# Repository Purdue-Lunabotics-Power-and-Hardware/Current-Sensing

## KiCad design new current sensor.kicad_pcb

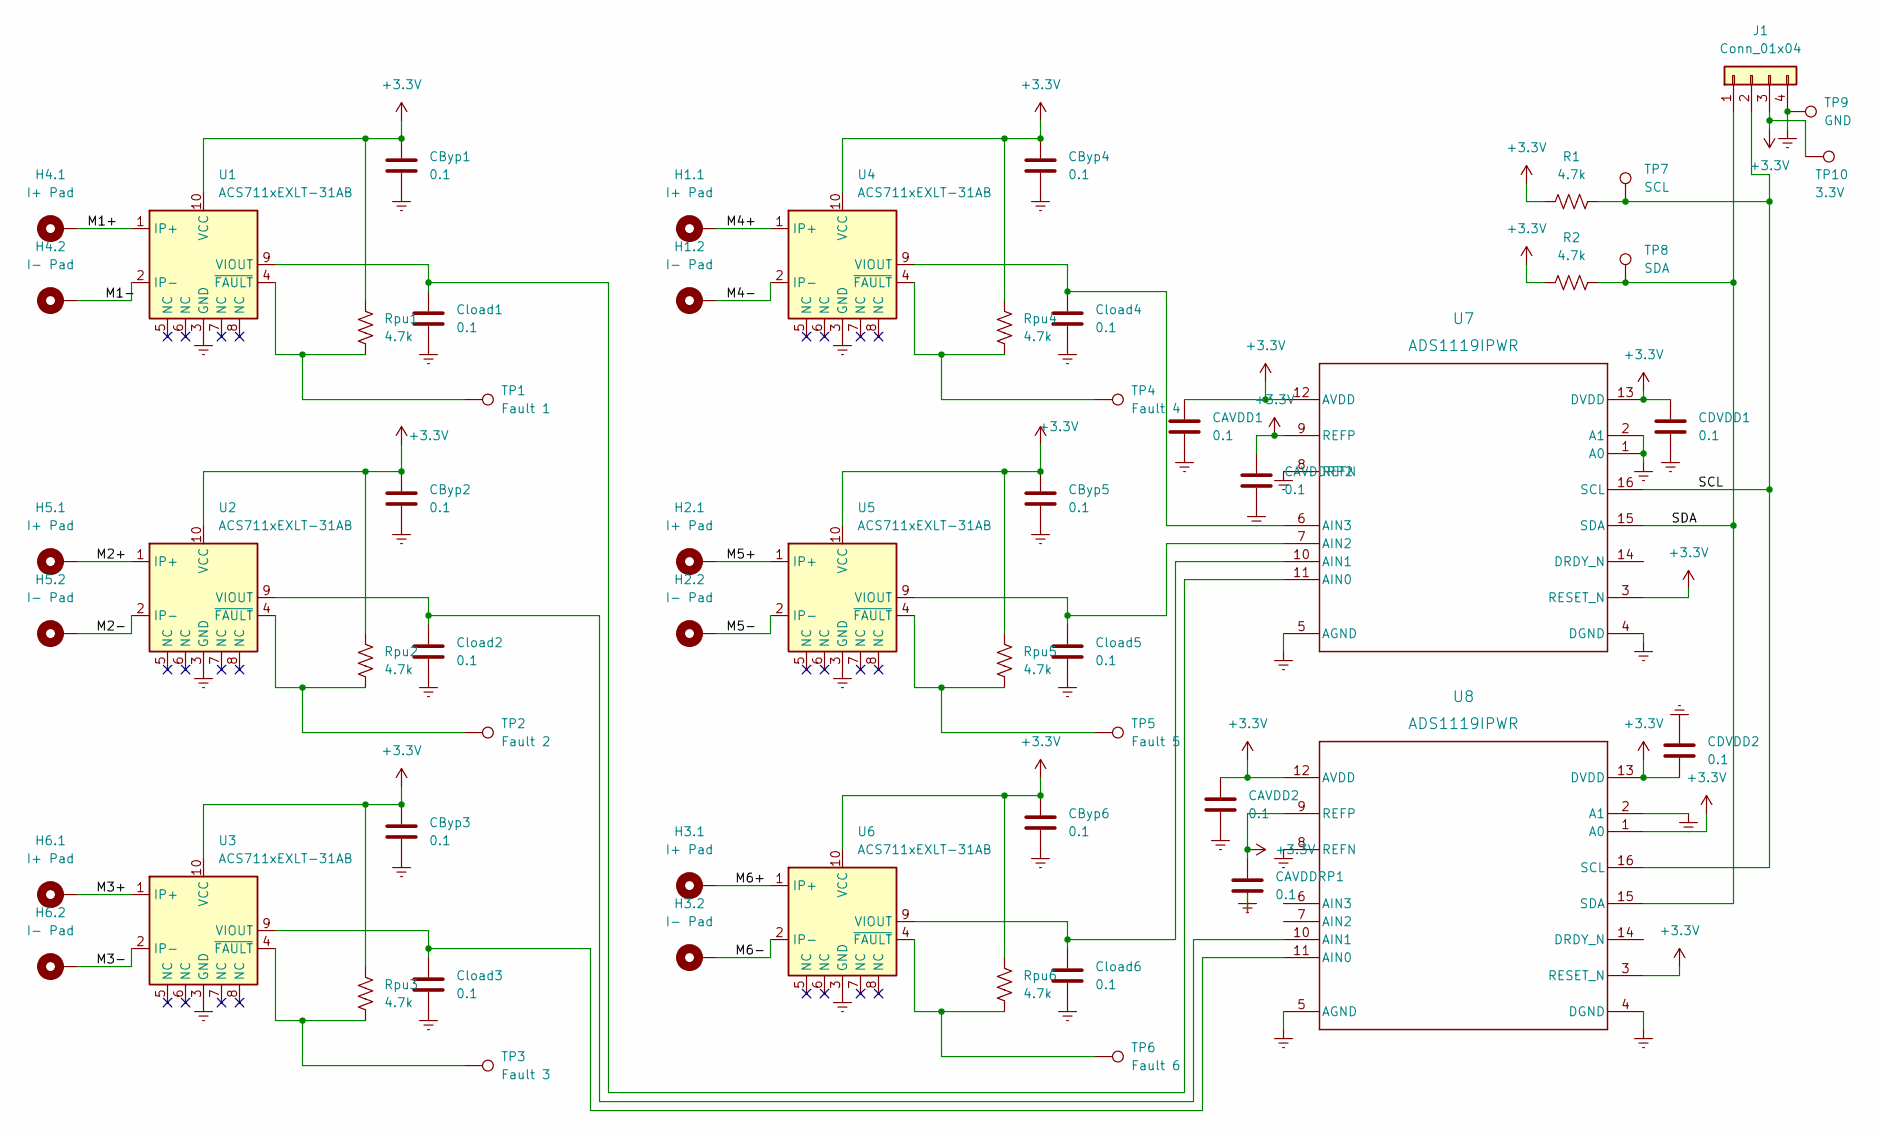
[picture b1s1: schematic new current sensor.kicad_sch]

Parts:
CAVDD1, CAVDD2: 0.1; C_0805_2012Metric_Pad1.18x1.45mm_HandSolder
CAVDDRP1, CAVDDRP2: 0.1; C_0805_2012Metric_Pad1.18x1.45mm_HandSolder
CByp1, CByp2, CByp3, CByp4, CByp5, CByp6: 0.1; C_0805_2012Metric_Pad1.18x1.45mm_HandSolder
CDVDD1, CDVDD2: 0.1; C_0805_2012Metric_Pad1.18x1.45mm_HandSolder
Cload1, Cload2, Cload3, Cload4, Cload5, Cload6: 0.1; C_0805_2012Metric_Pad1.18x1.45mm_HandSolder
H1.1, H2.1, H3.1, H4.1, H5.1, H6.1: I+ Pad; SolderWire-0.25sqmm_1x01_D0.65mm_OD2mm
H1.2, H2.2, H3.2, H4.2, H5.2, H6.2: I- Pad; SolderWire-0.25sqmm_1x01_D0.65mm_OD2mm
J1: Conn_01x04; JST_XH_S4B-XH-A_1x04_P2.50mm_Horizontal
R1, R2: 4.7k; R_0805_2012Metric_Pad1.20x1.40mm_HandSolder
Rpu1, Rpu2, Rpu3, Rpu4, Rpu5, Rpu6: 4.7k; R_0805_2012Metric_Pad1.20x1.40mm_HandSolder
TP1: Fault 1; SolderWire-0.1sqmm_1x01_D0.4mm_OD1mm
TP2: Fault 2; SolderWire-0.1sqmm_1x01_D0.4mm_OD1mm
TP3: Fault 3; SolderWire-0.1sqmm_1x01_D0.4mm_OD1mm
TP4: Fault 4; SolderWire-0.1sqmm_1x01_D0.4mm_OD1mm
TP5: Fault 5; SolderWire-0.1sqmm_1x01_D0.4mm_OD1mm
TP6: Fault 6; SolderWire-0.1sqmm_1x01_D0.4mm_OD1mm
TP7: SCL; SolderWire-0.1sqmm_1x01_D0.4mm_OD1mm
TP8: SDA; SolderWire-0.1sqmm_1x01_D0.4mm_OD1mm
TP9: GND; SolderWire-0.1sqmm_1x01_D0.4mm_OD1mm
TP10: 3.3V; SolderWire-0.1sqmm_1x01_D0.4mm_OD1mm
U1, U2, U3, U4, U5, U6: ACS711xEXLT-31AB; Allegro_QFN-12-10-1EP_3x3mm_P0.5mm
U7, U8: ADS1119IPWR; TSSOP-16_4.4x5mm_P0.65mm

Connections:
+3.3V: CAVDD1.1, CAVDD2.1, CAVDDRP1.1, CAVDDRP2.1, CByp1.1, CByp2.1, CByp3.1, CByp4.1, CByp5.1, CByp6.1, CDVDD1.1, CDVDD2.2, J1.3, R1.1, R2.1, Rpu1.1, Rpu2.1, Rpu3.1, Rpu4.1, Rpu5.1, Rpu6.1, TP10.1, U1.10 (VCC), U2.10 (VCC), U3.10 (VCC), U4.10 (VCC), U5.10 (VCC), U6.10 (VCC), U7.3 (RESET_N), U7.9 (REFP), U7.12 (AVDD), U7.13 (DVDD), U8.1 (A0), U8.3 (RESET_N), U8.9 (REFP), U8.12 (AVDD), U8.13 (DVDD)
/M1+: H4.1.1, U1.1 (IP+)
/M1-: H4.2.1, U1.2 (IP-)
/M2+: H5.1.1, U2.1 (IP+)
/M2-: H5.2.1, U2.2 (IP-)
/M3+: H6.1.1, U3.1 (IP+)
/M3-: H6.2.1, U3.2 (IP-)
/M4+: H1.1.1, U4.1 (IP+)
/M4-: H1.2.1, U4.2 (IP-)
/M5+: H2.1.1, U5.1 (IP+)
/M5-: H2.2.1, U5.2 (IP-)
/M6+: H3.1.1, U6.1 (IP+)
/M6-: H3.2.1, U6.2 (IP-)
/SCL: J1.2, R1.2, TP7.1, U7.16 (SCL), U8.16 (SCL)
/SDA: J1.1, R2.2, TP8.1, U7.15 (SDA), U8.15 (SDA)
Earth: CAVDD1.2, CAVDD2.2, CAVDDRP1.2, CAVDDRP2.2, CByp1.2, CByp2.2, CByp3.2, CByp4.2, CByp5.2, CByp6.2, CDVDD1.2, CDVDD2.1, Cload1.2, Cload2.2, Cload3.2, Cload4.2, Cload5.2, Cload6.2, J1.4, TP9.1, U1.3 (GND), U2.3 (GND), U3.3 (GND), U4.3 (GND), U5.3 (GND), U6.3 (GND), U7.1 (A0), U7.2 (A1), U7.4 (DGND), U7.5 (AGND), U7.8 (REFN), U8.2 (A1), U8.4 (DGND), U8.5 (AGND), U8.8 (REFN)
unnamed: Cload1.1, U1.9 (VIOUT), U7.11 (AIN0)
unnamed: Rpu1.2, TP1.1, U1.4 (~FAULT)
unnamed: Cload2.1, U2.9 (VIOUT), U8.10 (AIN1)
unnamed: Rpu2.2, TP2.1, U2.4 (~FAULT)
unnamed: Cload3.1, U3.9 (VIOUT), U8.11 (AIN0)
unnamed: Rpu3.2, TP3.1, U3.4 (~FAULT)
unnamed: Cload4.1, U4.9 (VIOUT), U7.6 (AIN3)
unnamed: Rpu4.2, TP4.1, U4.4 (~FAULT)
unnamed: Cload5.1, U5.9 (VIOUT), U7.7 (AIN2)
unnamed: Rpu5.2, TP5.1, U5.4 (~FAULT)
unnamed: Cload6.1, U6.9 (VIOUT), U7.10 (AIN1)
unnamed: Rpu6.2, TP6.1, U6.4 (~FAULT)

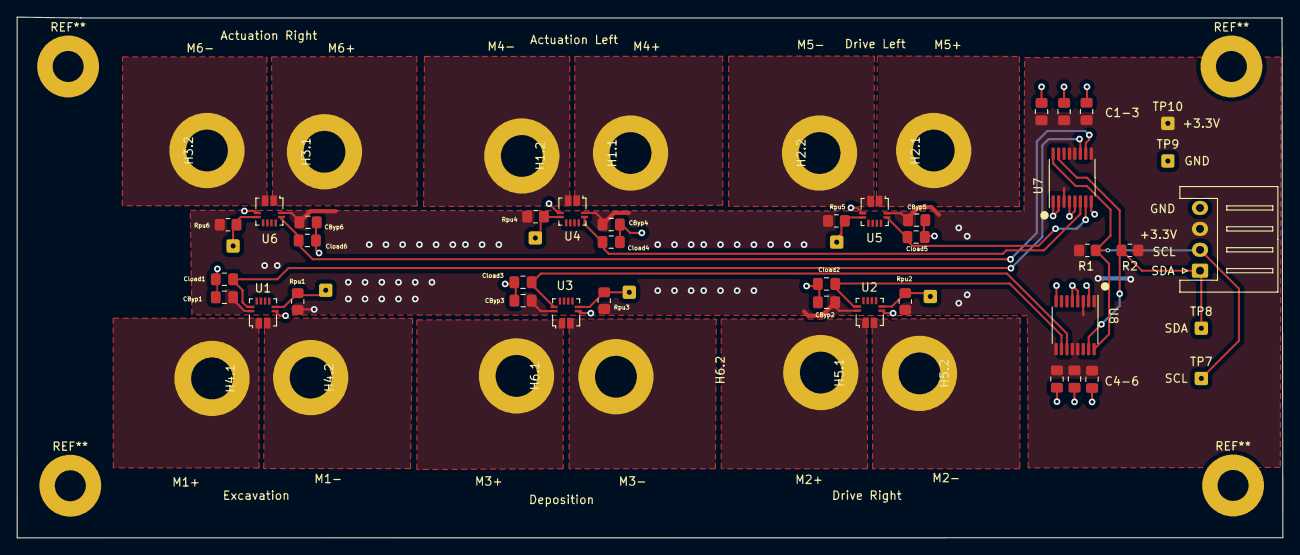
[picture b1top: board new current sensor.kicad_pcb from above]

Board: 2 copper layers, 151.3 x 62.3 mm, 57 parts (0 on the bottom side), 28 nets.

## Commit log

2023-10-31 Labels updated
2023-10-31 Labels updated with final(hopefully) parts
2023-11-08 Start Traces
2024-01-10 Clear for final review revision
2024-01-10 Final review revisions
    Fixed DRC errors and clearance problems, removed thermal relief
2024-01-13 final tweaks before ordering
2024-01-25 Added text labels and made some components larger
2024-01-27 Fixed andgled wire on U7 wire
2024-01-27 mounting holes mounting holes
2024-03-23 Reference pad update
2024-03-26 midway point
2024-03-26 3/26 ready for revision
2024-03-27 added a 3.3v plane to the back
2024-03-27 final changes
2024-03-27 added tps
2024-03-27 done now
